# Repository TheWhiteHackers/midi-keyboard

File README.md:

# midi-keyboard
A custom MIDI keyboard with switches, sliders, rotary encoders, neo pixels, and capacitive touch!
Once it gets built, it will play music!

This is what my keyboard looks like!

## parts used
- EC11 Rotary Encoders
- SK6812 MINI-E Neopixels
- Bourns Slide Potentiometers
- Kailh Choc Low-Profile Switches

## project images

Here is the back of the silkscreen. Here I have added space themed pictures using KiCads iamge converter.

Here is the front of the silkscreen. I continued witht the same theme, however all images are in circles.

This is what my schematic editor looked like once I was done

Hack Life Week 3 Project - DESIGN YOUR INSTRUMENT

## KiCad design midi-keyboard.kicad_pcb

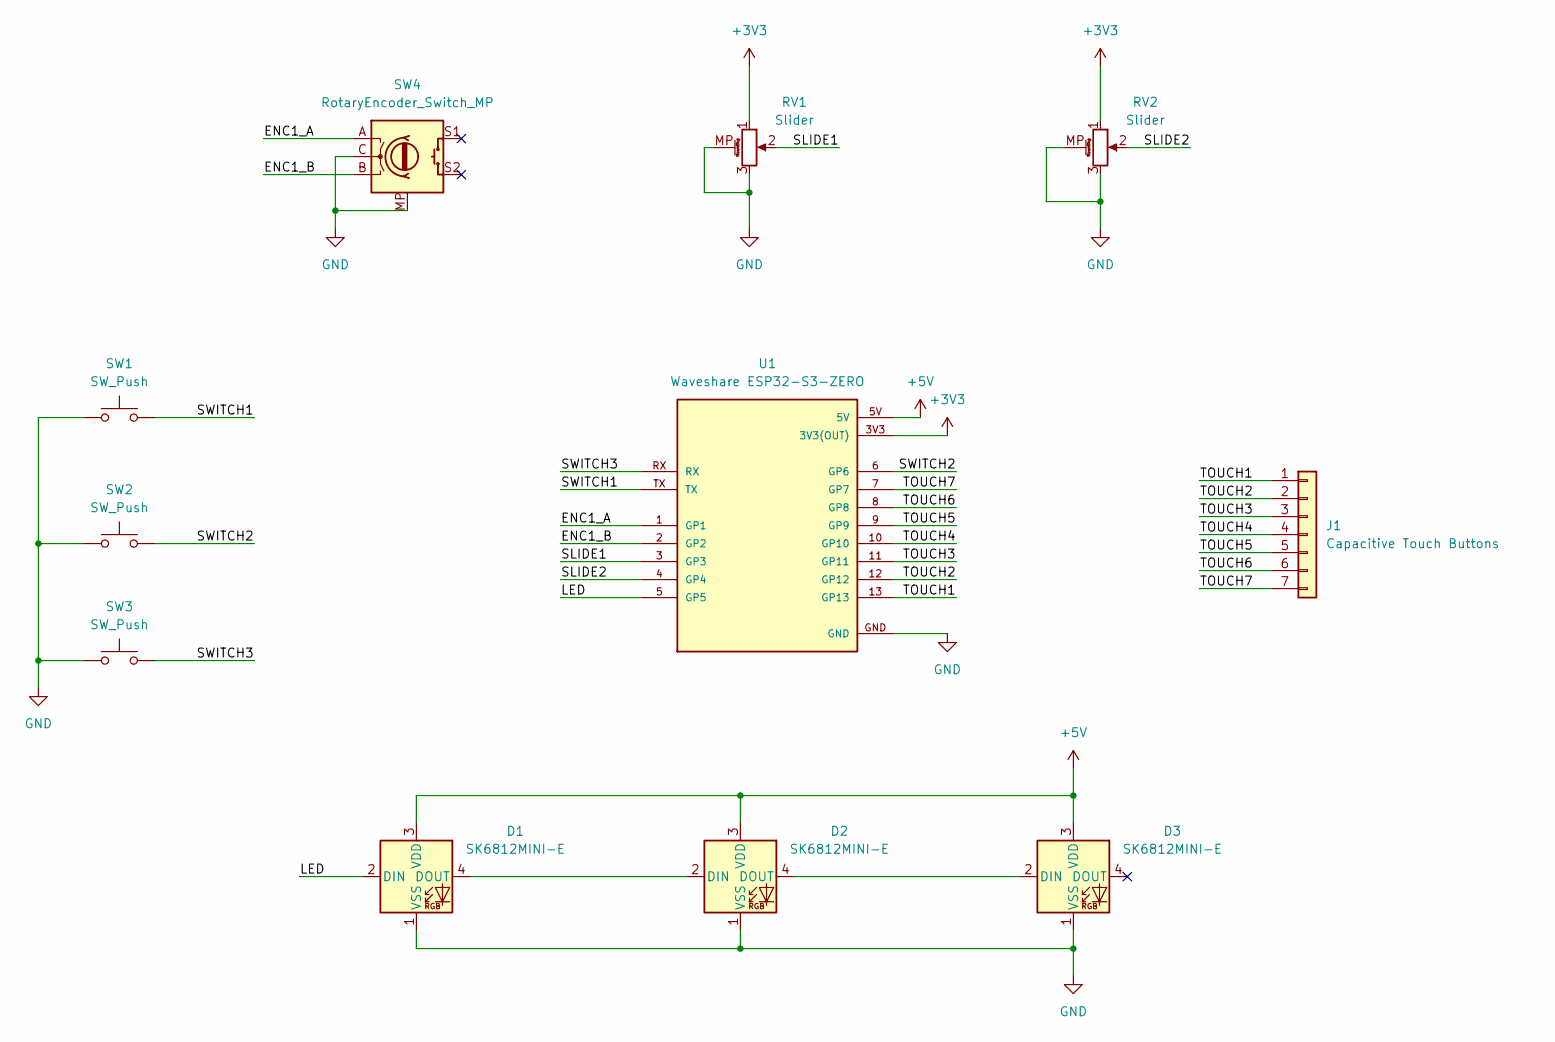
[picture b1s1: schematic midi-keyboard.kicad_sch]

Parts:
D1, D2, D3: SK6812MINI-E; LED_SK6812MINI-E_3.2x2.8mm_P1.5mm_ReverseMount
J1: Capacitive Touch Buttons; Capacitive Keys
RV1, RV2: Slider; Potentiometer_Bourns_PTA1543_Single_Slide
SW1, SW2, SW3: SW_Push; Kailh Choc Low-Profile Switches
SW4: RotaryEncoder_Switch_MP; RotaryEncoder_Alps_EC12E-Switch_Vertical_H20mm_CircularMoun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
U1: Waveshare ESP32-S3-ZERO; Waveshare ESP32-S3-Zero; PARTREV NA

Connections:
+3V3: RV1.1, RV2.1, U1.3V3 (3V3(OUT))
+5V: D1.3 (VDD), D2.3 (VDD), D3.3 (VDD), U1.5V
/ENC1_A: SW4.A, U1.1 (GP1)
/ENC1_B: SW4.B, U1.2 (GP2)
/LED: D1.2 (DIN), U1.5 (GP5)
/SLIDE1: RV1.2, U1.3 (GP3)
/SLIDE2: RV2.2, U1.4 (GP4)
/SWITCH1: SW1.2, U1.TX
/SWITCH2: SW2.2, U1.6 (GP6)
/SWITCH3: SW3.2, U1.RX
/TOUCH1: J1.1, U1.13 (GP13)
/TOUCH2: J1.2, U1.12 (GP12)
/TOUCH3: J1.3, U1.11 (GP11)
/TOUCH4: J1.4, U1.10 (GP10)
/TOUCH5: J1.5, U1.9 (GP9)
/TOUCH6: J1.6, U1.8 (GP8)
/TOUCH7: J1.7, U1.7 (GP7)
GND: D1.1 (VSS), D2.1 (VSS), D3.1 (VSS), RV1.3, RV1.MP (MountPin), RV2.3, RV2.MP (MountPin), SW1.1, SW2.1, SW3.1, SW4.C, SW4.MP, U1.GND
unnamed: D1.4 (DOUT), D2.2 (DIN)
unnamed: D2.4 (DOUT), D3.2 (DIN)

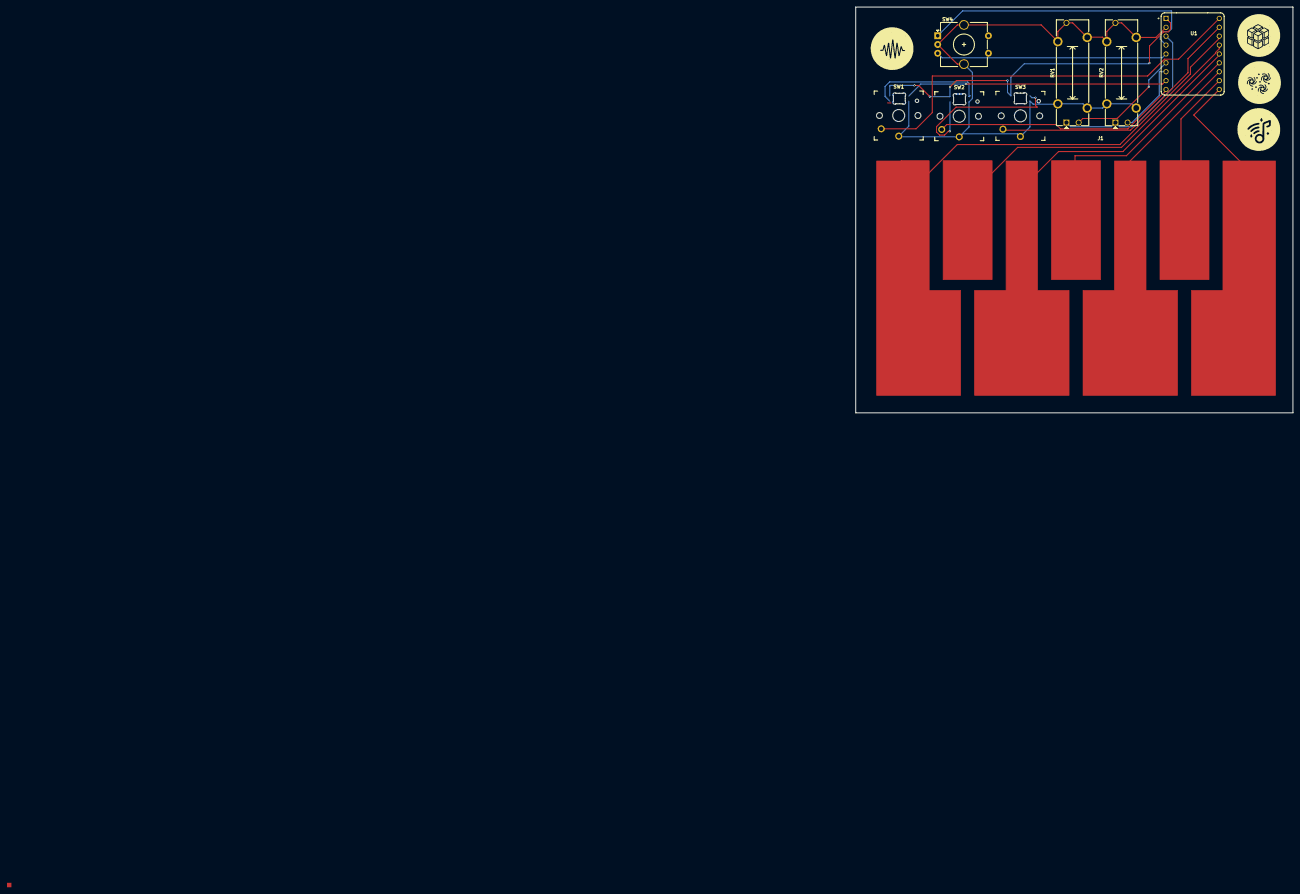
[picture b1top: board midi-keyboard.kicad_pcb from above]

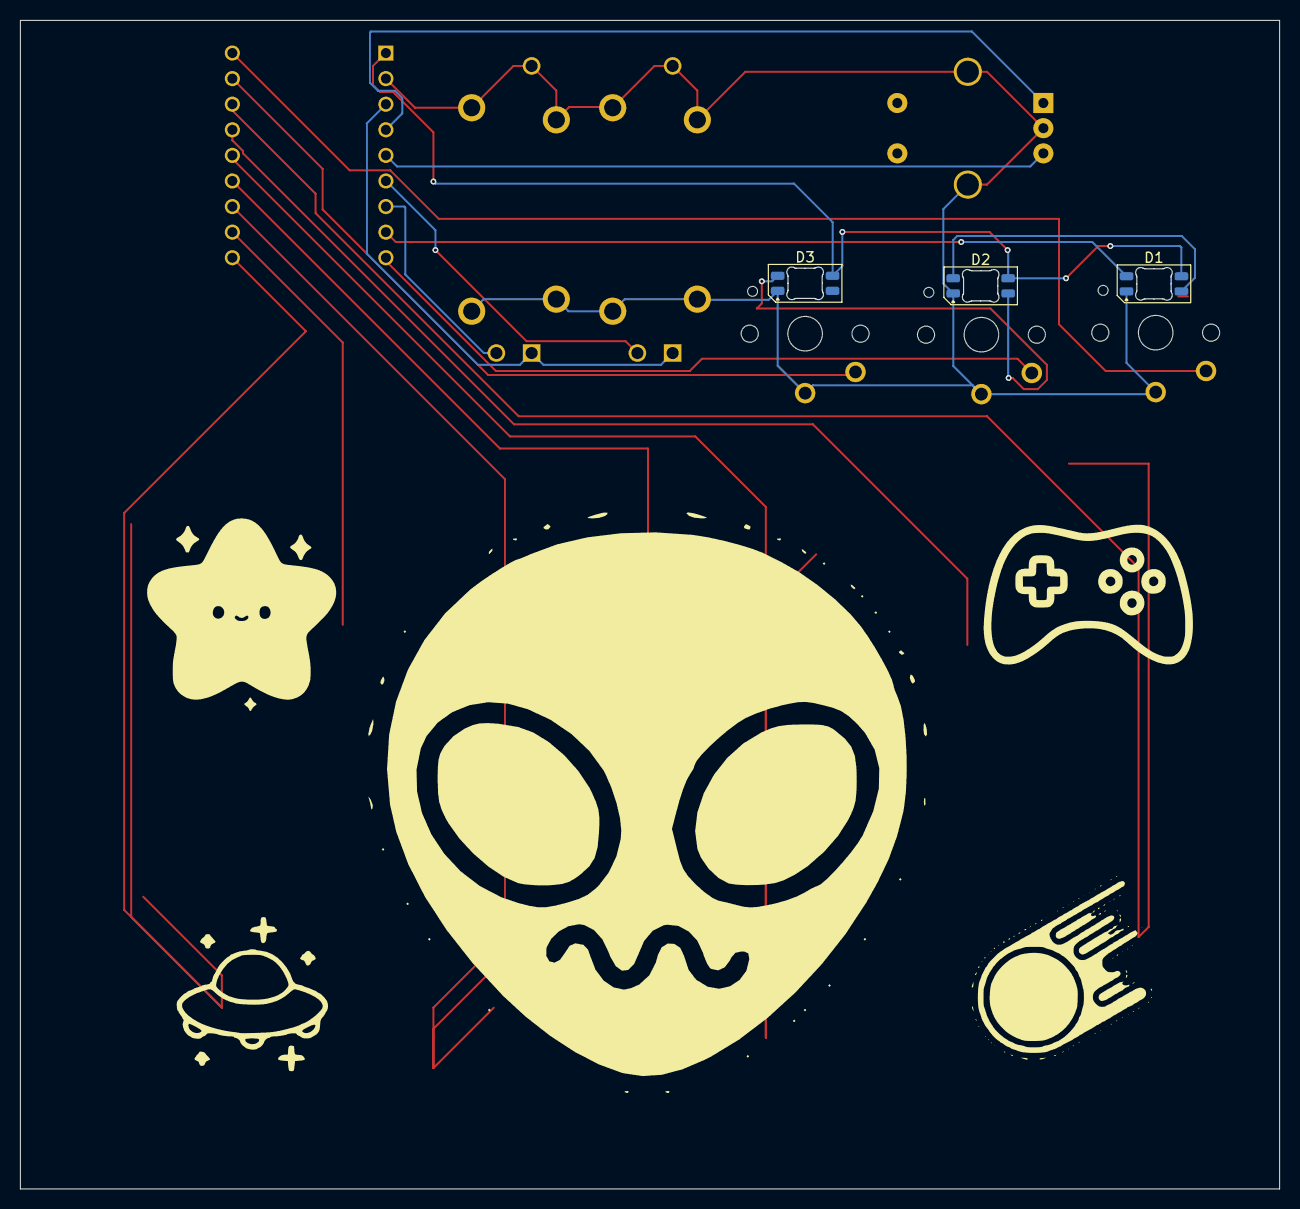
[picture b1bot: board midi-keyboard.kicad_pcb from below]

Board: 2 copper layers, 125.0 x 116.0 mm, 11 parts (3 on the bottom side), 20 nets.
